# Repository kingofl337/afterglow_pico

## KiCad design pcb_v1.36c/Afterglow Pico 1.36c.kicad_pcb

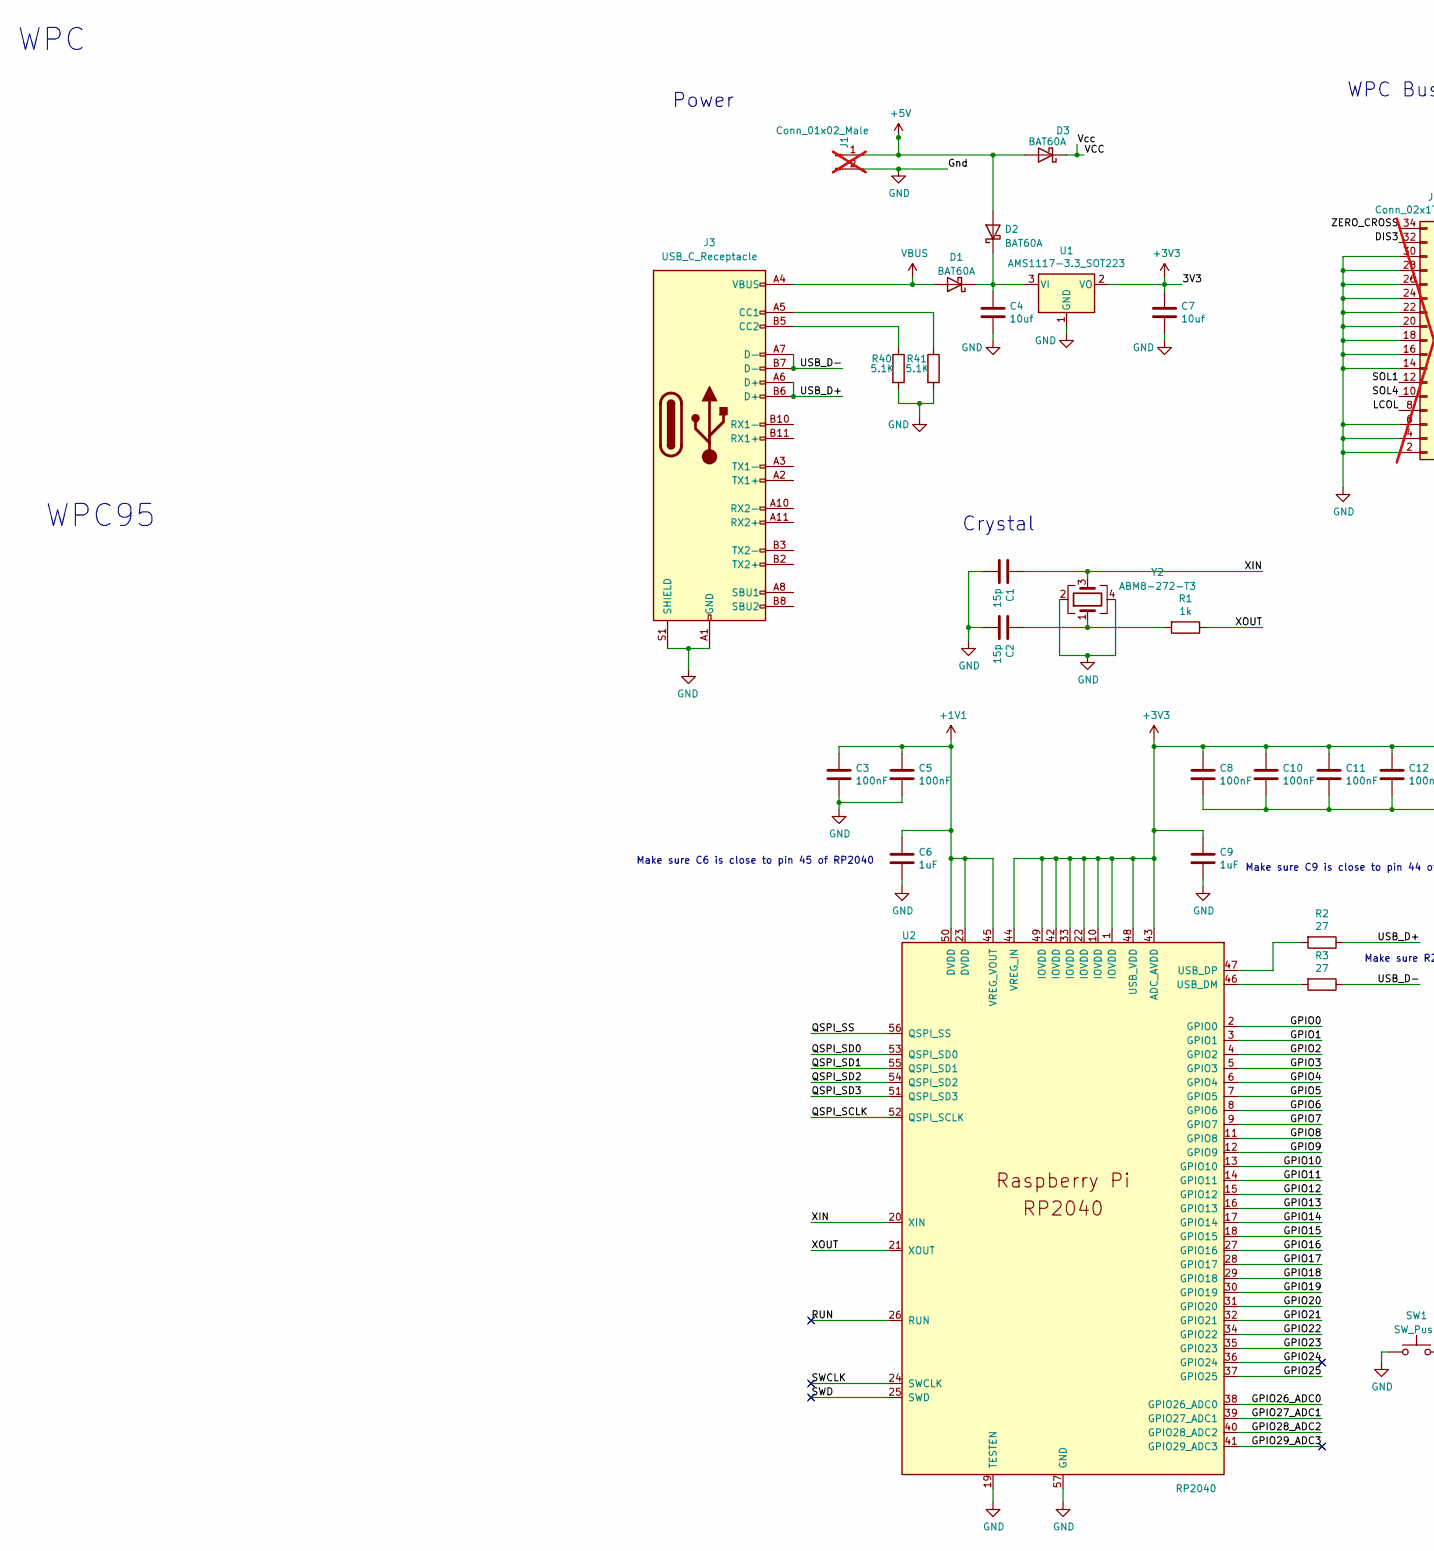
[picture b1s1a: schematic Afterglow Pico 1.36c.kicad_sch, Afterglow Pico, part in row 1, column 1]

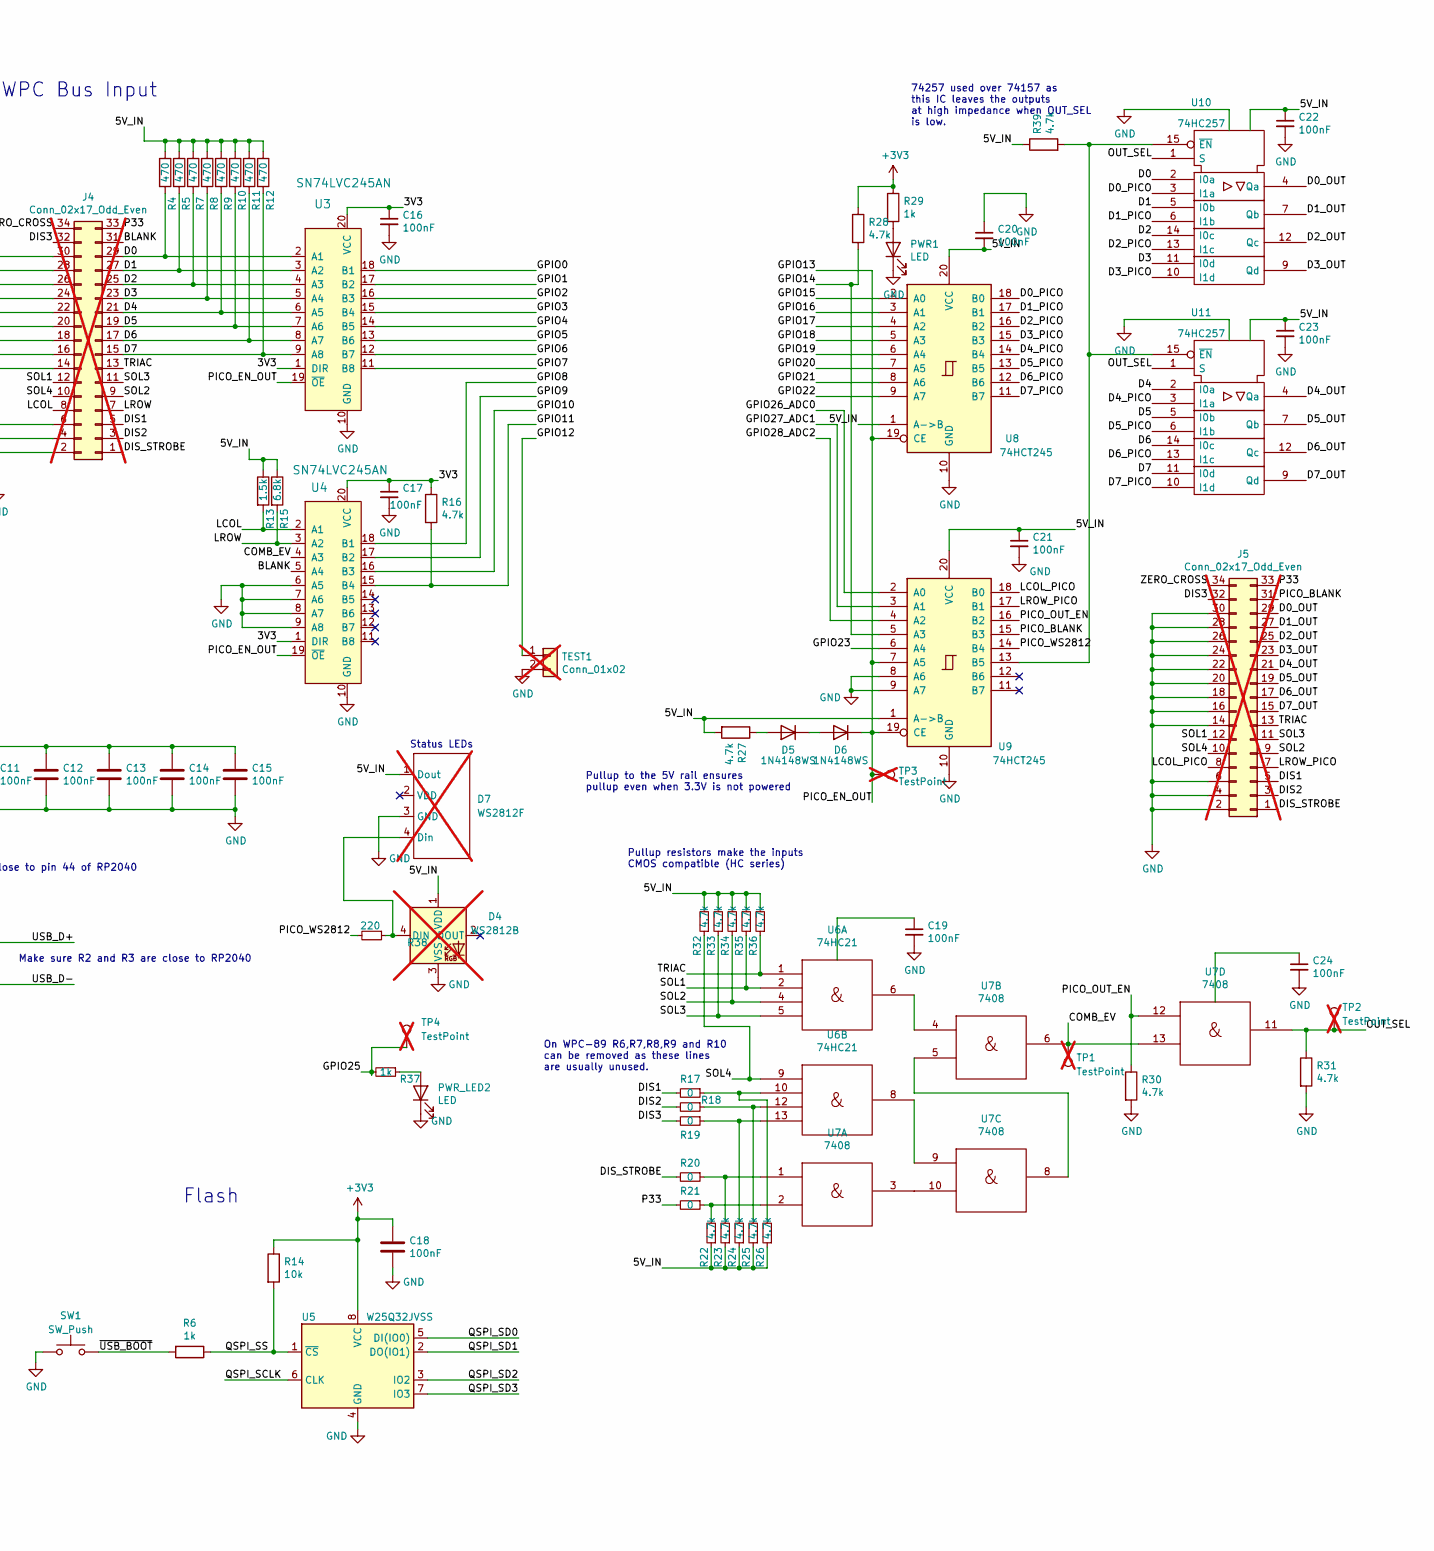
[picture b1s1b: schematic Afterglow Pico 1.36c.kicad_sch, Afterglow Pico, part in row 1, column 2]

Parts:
C1, C2: 15p; C_0603_1608Metric; LCSC Part # C1644
C3, C5, C8, C10, C11, C12, C13, C14, C15, C16, C17, C18, C19, C20, C21, C22, C23, C24: 100nF; C_0402_1005Metric; LCSC Part # C307331
C4, C7: 10uf; C_0805_2012Metric; LCSC Part # C15850
C6, C9: 1uF; C_0402_1005Metric; LCSC Part # C52923
D1, D2, D3: BAT60A; D_SOD-323; LCSC Part # C513277
D4: WS2812B; LED_WS2812B_PLCC4_5.0x5.0mm_P3.2mm; LCSC Part # C2761795; not fitted
D5, D6: 1N4148WS; D_SOD-323; LCSC Part # C2128
D7: WS2812F; WS2812D-F5; not fitted
J1: Conn_01x02_Male; Molex_KK-254_AE-6410-02A_1x02_P2.54mm_Vertical; not fitted
J3: USB_C_Receptacle; USB_C_Receptacle_Molex_105450-0101; LCSC Part # C134092
J4: Conn_02x17_Odd_Even; PinHeader_2x17_P2.54mm_Vertical; not fitted
J5: Conn_02x17_Odd_Even; PinHeader_2x17_P2.54mm_Vertical; LCSC Part # C2894978; not fitted
PWR1: LED; LED_0603_1608Metric; LCSC Part # C2290
PWR_LED2: LED; LED_0603_1608Metric; LCSC Part # C2290
R1, R6, R29, R37: 1k; R_0402_1005Metric; LCSC Part # C11702
R2, R3: 27; R_0402_1005Metric; LCSC Part # C25100
R4, R5, R7, R8, R9, R10, R11, R12: 470; R_0402_1005Metric; LCSC Part # C25117
R13: 1.5k; R_0402_1005Metric; LCSC Part # C25867
R14: 10k; R_0402_1005Metric; LCSC Part # C25744
R15: 6.8k; R_0402_1005Metric; LCSC Part # C25917
R16, R22, R23, R24, R25, R26, R27, R28, R30, R31, R32, R33, R34, R35, R36, R39: 4.7k; R_0402_1005Metric; LCSC Part # C25900
R17, R18, R19, R20, R21: 0; R_0402_1005Metric; LCSC Part # C17168
R38: 220; R_0402_1005Metric; LCSC Part # C25091
R40, R41: 5.1K; R_0603_1608Metric; LCSC Part # C23186
SW1: SW_Push; SW_SPST_B3U-1000P; LCSC Part # C231329
TEST1: Conn_01x02; PinHeader_1x02_P2.54mm_Vertical; LCSC Part # C124375; not fitted
TP1, TP2, TP3, TP4: TestPoint; TestPoint_Loop_D1.80mm_Drill1.0mm_Beaded; not fitted
U1: AMS1117-3.3_SOT223; SOT-223-3_TabPin2; LCSC Part # C6186
U2: RP2040; RP2040-QFN-56; LCSC Part # C2040
U3, U4: SN74LVC245AN; TSSOP-20_4.4x6.5mm_P0.65mm; MPN SN74LVC245AN; Digi-Key_PN 296-8503-5-ND
U5: W25Q32JVSS; SOIC-8_5.23x5.23mm_P1.27mm; LCSC Part # C82344
U6: 74HC21; SOIC-14_3.9x8.7mm_P1.27mm; LCSC Part # C75398
U7: 7408; SOIC-14_3.9x8.7mm_P1.27mm; LCSC Part # C5593
U8, U9: 74HCT245; TSSOP-20_4.4x6.5mm_P0.65mm; LCSC Part # C6779
U10, U11: 74HC257; TSSOP-16_4.4x5mm_P0.65mm; LCSC Part # C2868824
Y2: ABM8-272-T3; Crystal_SMD_Abracon_ABM8AIG-4Pin_3.2x2.5mm; LCSC Part # C20625731

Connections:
+1V1: C3.1, C5.1, C6.1, U2.23 (DVDD), U2.45 (VREG_VOUT), U2.50 (DVDD)
+3V3: C7.1, C8.1, C9.1, C10.1, C11.1, C12.1, C13.1, C14.1, C15.1, C16.1, C17.1, C18.1, R14.1, R16.1, R28.1, R29.1, U1.2 (VO), U2.1 (IOVDD), U2.10 (IOVDD), U2.22 (IOVDD), U2.33 (IOVDD), U2.42 (IOVDD), U2.43 (ADC_AVDD), U2.44 (VREG_IN), U2.48 (USB_VDD), U2.49 (IOVDD), U3.1 (DIR), U3.20 (VCC), U4.1 (DIR), U4.20 (VCC), U5.8 (VCC)
+5V: D2.2 (A), D3.2 (A), J1.1
/BLANK: J4.31, U4.5 (A4)
/COMB_EV: TP1.1, U4.4 (A3), U7.6, U7.13
/D0: J4.29, R4.2, U3.2 (A1), U10.2 (I0a)
/D0_OUT: J5.29, U10.4 (Qa)
/D0_PICO: U8.18 (B0), U10.3 (I1a)
/D1: J4.27, R5.2, U3.3 (A2), U10.5 (I0b)
/D1_OUT: J5.27, U10.7 (Qb)
/D1_PICO: U8.17 (B1), U10.6 (I1b)
/D2: J4.25, R7.2, U3.4 (A3), U10.14 (I0c)
/D2_OUT: J5.25, U10.12 (Qc)
/D2_PICO: U8.16 (B2), U10.13 (I1c)
/D3: J4.23, R8.2, U3.5 (A4), U10.11 (I0d)
/D3_OUT: J5.23, U10.9 (Qd)
/D3_PICO: U8.15 (B3), U10.10 (I1d)
/D4: J4.21, R9.2, U3.6 (A5), U11.2 (I0a)
/D4_OUT: J5.21, U11.4 (Qa)
/D4_PICO: U8.14 (B4), U11.3 (I1a)
/D5: J4.19, R10.2, U3.7 (A6), U11.5 (I0b)
/D5_OUT: J5.19, U11.7 (Qb)
/D5_PICO: U8.13 (B5), U11.6 (I1b)
/D6: J4.17, R11.2, U3.8 (A7), U11.14 (I0c)
/D6_OUT: J5.17, U11.12 (Qc)
/D6_PICO: U8.12 (B6), U11.13 (I1c)
/D7: J4.15, R12.2, U3.9 (A8), U11.11 (I0d)
/D7_OUT: J5.15, U11.9 (Qd)
/D7_PICO: U8.11 (B7), U11.10 (I1d)
/DIS1: J4.5, J5.5, R17.2
/DIS2: J4.3, J5.3, R18.2
/DIS3: J4.32, J5.32, R19.2
/DIS_STROBE: J4.1, J5.1, R20.2
/GPIO0: U2.2 (GPIO0), U3.18 (B1)
/GPIO1: U2.3 (GPIO1), U3.17 (B2)
/GPIO2: U2.4 (GPIO2), U3.16 (B3)
/GPIO3: U2.5 (GPIO3), U3.15 (B4)
/GPIO4: U2.6 (GPIO4), U3.14 (B5)
/GPIO5: U2.7 (GPIO5), U3.13 (B6)
/GPIO6: U2.8 (GPIO6), U3.12 (B7)
/GPIO7: U2.9 (GPIO7), U3.11 (B8)
/GPIO8: U2.11 (GPIO8), U4.18 (B1)
/GPIO9: U2.12 (GPIO9), U4.17 (B2)
/GPIO10: U2.13 (GPIO10), U4.16 (B3)
/GPIO11: R16.2, U2.14 (GPIO11), U4.15 (B4)
/GPIO12: TEST1.1, U2.15 (GPIO12)
/GPIO13: D6.1 (K), TP3.1, U2.16 (GPIO13), U3.19 (~OE), U4.19 (~OE), U8.19 (CE), U9.7 (A5), U9.19 (CE)
/GPIO14: R28.2, U2.17 (GPIO14), U9.5 (A3)
/GPIO15: U2.18 (GPIO15), U8.2 (A0)
/GPIO16: U2.27 (GPIO16), U8.3 (A1)
/GPIO17: U2.28 (GPIO17), U8.4 (A2)
/GPIO18: U2.29 (GPIO18), U8.5 (A3)
/GPIO19: U2.30 (GPIO19), U8.6 (A4)
/GPIO20: U2.31 (GPIO20), U8.7 (A5)
/GPIO21: U2.32 (GPIO21), U8.8 (A6)
/GPIO22: U2.34 (GPIO22), U8.9 (A7)
/GPIO23: U2.35 (GPIO23), U9.6 (A4)
/GPIO24: U2.36 (GPIO24)
/GPIO25: R37.2, TP4.1, U2.37 (GPIO25)
/GPIO26_ADC0: U2.38 (GPIO26_ADC0), U9.2 (A0)
/GPIO27_ADC1: U2.39 (GPIO27_ADC1), U9.3 (A1)
/GPIO28_ADC2: U2.40 (GPIO28_ADC2), U9.4 (A2)
/GPIO29_ADC3: U2.41 (GPIO29_ADC3)
/LCOL: J4.8, R13.2, U4.2 (A1)
/LCOL_PICO: J5.8, U9.18 (B0)
/LROW: J4.7, R15.2, U4.3 (A2)
/LROW_PICO: J5.7, U9.17 (B1)
/OUT_SEL: R31.1, TP2.1, U7.11, U10.1 (S), U11.1 (S)
/P33: J4.33, J5.33, R21.2
/PICO_BLANK: J5.31, U9.15 (B3)
/PICO_OUT_EN: R30.1, U7.12, U9.16 (B2)
/PICO_WS2812: R38.2, U9.14 (B4)
/QSPI_SCLK: U2.52 (QSPI_SCLK), U5.6 (CLK)
/QSPI_SD0: U2.53 (QSPI_SD0), U5.5 (DI(IO0))
/QSPI_SD1: U2.55 (QSPI_SD1), U5.2 (DO(IO1))
/QSPI_SD2: U2.54 (QSPI_SD2), U5.3 (IO2)
/QSPI_SD3: U2.51 (QSPI_SD3), U5.7 (IO3)
/QSPI_SS: R6.1, R14.2, U2.56 (QSPI_SS), U5.1 (~CS)
/RUN: U2.26 (RUN)
/SOL1: J4.12, J5.12, R35.1, U6.2
/SOL2: J4.9, J5.9, R34.1, U6.4
/SOL3: J4.11, J5.11, R33.1, U6.5
/SOL4: J4.10, J5.10, R32.1, U6.9
/SWCLK: U2.24 (SWCLK)
/SWD: U2.25 (SWD)
/TRIAC: J4.13, J5.13, R36.1, U6.1
/USB_D+: J3.A6 (D+), J3.B6 (D+), R2.1
/USB_D-: J3.A7 (D-), J3.B7 (D-), R3.1
/XIN: C1.1, U2.20 (XIN), Y2.3
/XOUT: R1.1, U2.21 (XOUT)
/ZERO_CROSS: J4.34, J5.34
/~USB_BOOT: R6.2, SW1.2
GND: C1.2, C2.2, C3.2, C4.2, C5.2, C6.2, C7.2, C8.2, C9.2, C10.2, C11.2, C12.2, C13.2, C14.2, C15.2, C16.2, C17.2, C18.2, C19.2, C20.1, C21.2, C22.2, C23.2, C24.2, D4.3 (VSS), D7.3 (GND), J1.2, J3.A1 (GND), J3.A12 (GND), J3.B1 (GND), J3.B12 (GND), J3.S1 (SHIELD), J4.2, J4.4, J4.6, J4.14, J4.16, J4.18, J4.20, J4.22, J4.24, J4.26, J4.28, J4.30, J5.2, J5.4, J5.6, J5.14, J5.16, J5.18, J5.20, J5.22, J5.24, J5.26, J5.28, J5.30, PWR1.1 (K), PWR_LED2.1 (K), R30.2, R31.2, R40.2, R41.2, SW1.1, TEST1.2, U1.1 (GND), U2.19 (TESTEN), U2.57 (GND), U3.10 (GND), U4.6 (A5), U4.7 (A6), U4.8 (A7), U4.9 (A8), U4.10 (GND), U5.4 (GND), U6.7 (Gnd), U7.7 (Gnd), U8.10 (GND), U9.8 (A6), U9.9 (A7), U9.10 (GND), U10.8 (GND), U11.8 (GND), Y2.2, Y2.4
unnamed: C2.1, R1.2, Y2.1
unnamed: C4.1, D1.1 (K), D2.1 (K), U1.3 (VI)
unnamed: D4.4 (DIN), D7.4 (Din), R38.1
unnamed: D5.2 (A), R27.1
unnamed: D5.1 (K), D6.2 (A)
unnamed: J3.A5 (CC1), R41.1
unnamed: J3.B5 (CC2), R40.1
unnamed: PWR1.2 (A), R29.2
unnamed: PWR_LED2.2 (A), R37.1
unnamed: R17.1, R26.2, U6.10
unnamed: R18.1, R25.2, U6.12
unnamed: R19.1, R24.2, U6.13
unnamed: R20.1, R23.2, U7.1
unnamed: R21.1, R22.2, U7.2
unnamed: R3.2, U2.46 (USB_DM)
unnamed: R2.2, U2.47 (USB_DP)
unnamed: U6.6, U7.4
unnamed: U6.8, U7.9
unnamed: U7.5, U7.8
unnamed: U7.3, U7.10
unnamed: R39.2, U9.13 (B5), U10.15 (~EN), U11.15 (~EN)
VBUS: D1.2 (A), J3.A4 (VBUS), J3.A9 (VBUS), J3.B4 (VBUS), J3.B9 (VBUS)

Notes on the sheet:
WPC
Pullup to the 5V rail ensures pullup even when 3.3V is not powered
Status LEDs
Pullup resistors make the inputs CMOS compatible (HC series)
Make sure C9 is close to pin 44 of RP2040
Power
Crystal
74257 used over 74157 as this IC leaves the outputs at high impedance when OUT_SEL is low.
On WPC-89 R6,R7,R8,R9 and R10 can be removed as these lines are usually unused.
WPC Bus Input
WPC95
Make sure R2 and R3 are close to RP2040
Flash
Make sure C6 is close to pin 45 of RP2040

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
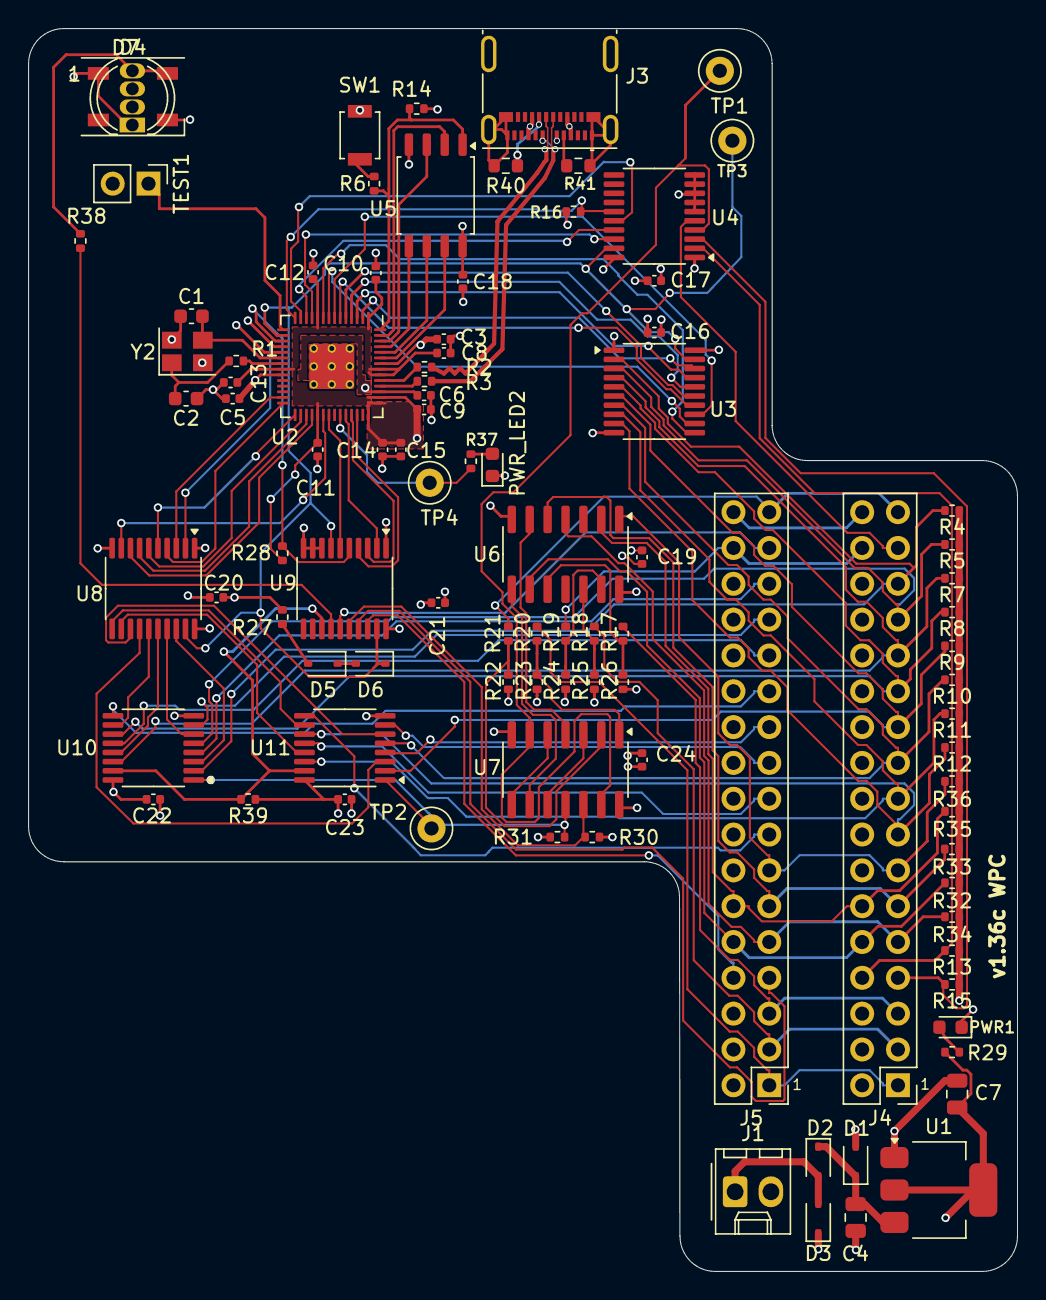
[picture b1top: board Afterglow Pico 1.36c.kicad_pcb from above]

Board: 4 copper layers, 70.1 x 88.1 mm, 96 parts (0 on the bottom side), 111 nets.
